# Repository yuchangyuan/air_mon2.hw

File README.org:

#+title: A simple air monitor with multiple sensor

+ data collect with nodemcu-32s
+ WZ-H3/WZ-H3-K for HCOH
+ SGP30 for CO2 & TVOC
+ SHT3X for humidity compensations
+ PMS7003 for PM2.5

current version is v1.1, all sensor works:

+ only test with WZ-H3(manully soldering 2.54mm pin)
+ distance between SHT3X & ESP32 module is too small, cause measured temperature much higher than actual ambient temperature.

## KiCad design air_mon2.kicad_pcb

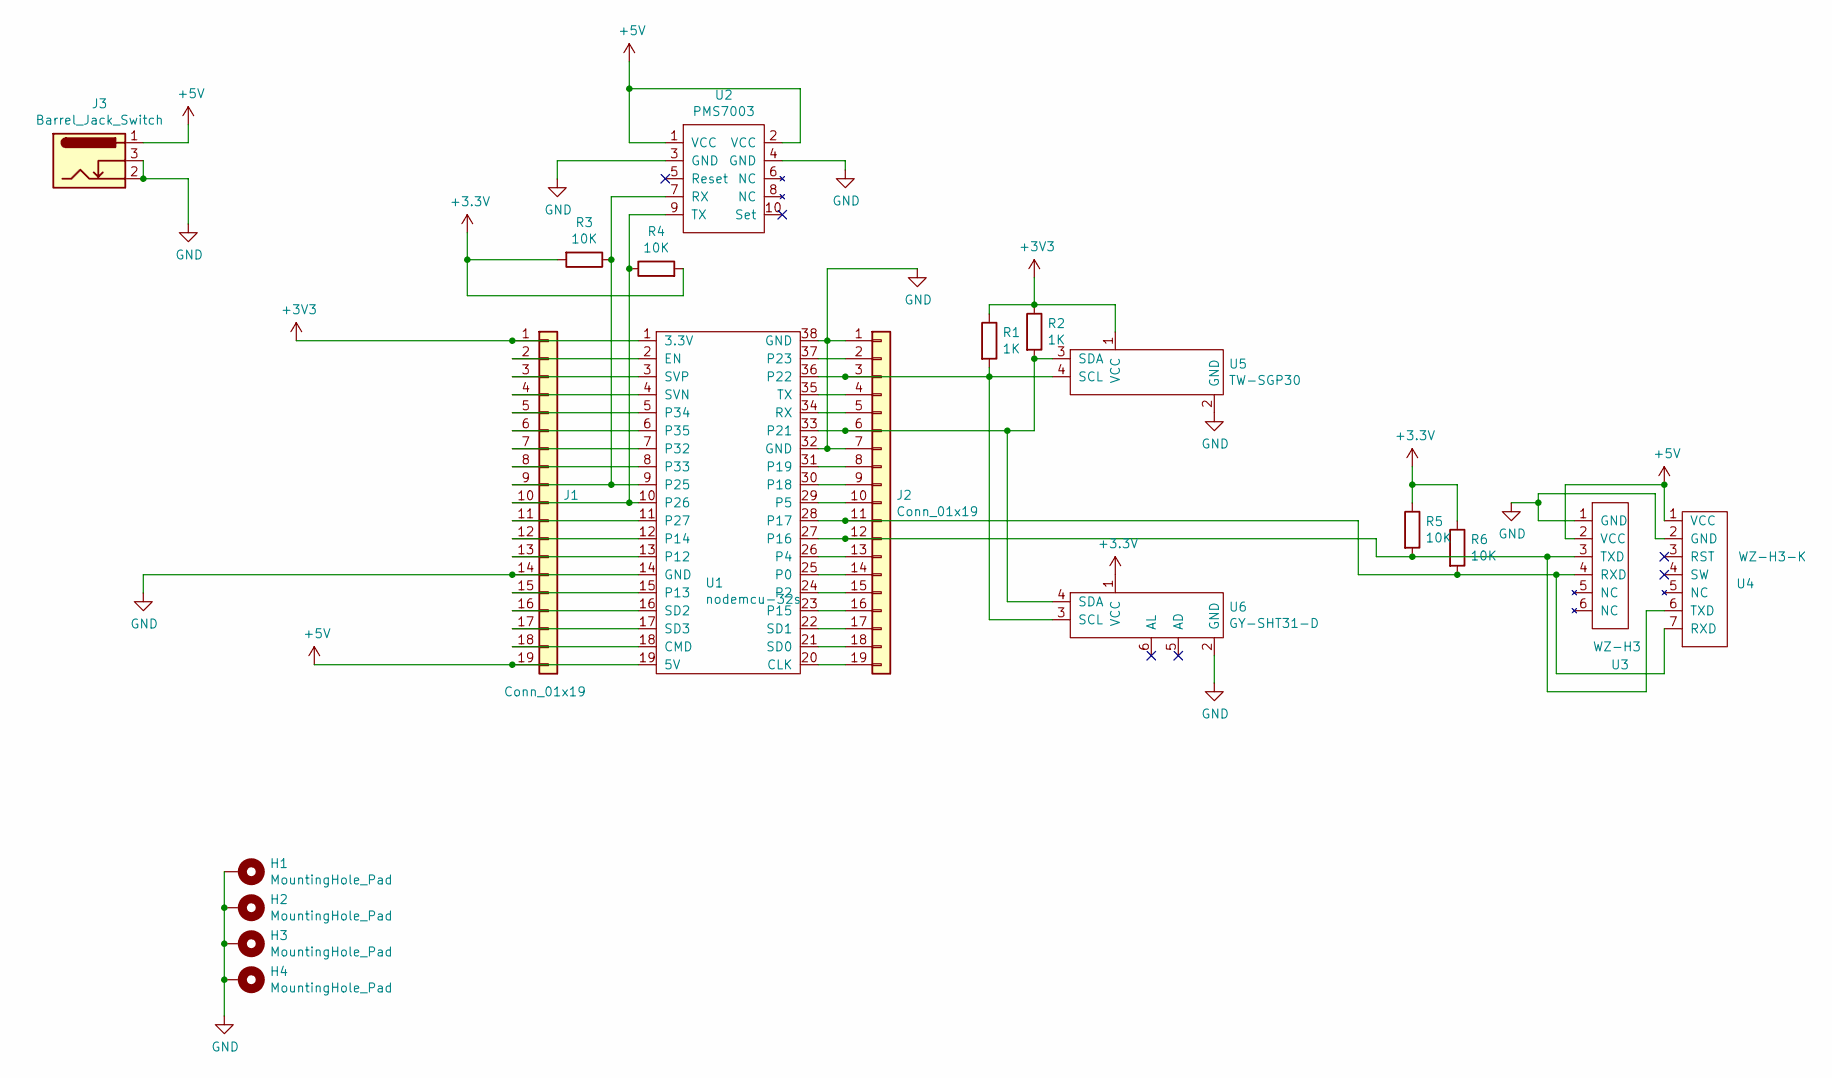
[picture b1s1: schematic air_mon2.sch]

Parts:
H1, H2, H3, H4: MountingHole_Pad; MountingHole_2.2mm_M2_Pad
J1, J2: Conn_01x19; PinHeader_1x19_P2.54mm_Vertical
J3: Barrel_Jack_Switch; BarrelJack_Horizontal
R1, R2: 1K; R_0805_2012Metric_Pad1.20x1.40mm_HandSolder
R3, R4, R5, R6: 10K; R_0805_2012Metric_Pad1.20x1.40mm_HandSolder
U1: nodemcu-32s
U2: PMS7003
U3: WZ-H3
U4: WZ-H3-K
U5: TW-SGP30
U6: GY-SHT31-D

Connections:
+5V: J1.19, J3.1, U1.19 (5V), U2.1 (VCC), U2.2 (VCC), U3.2 (VCC), U4.1 (VCC)
GND: H1.1, H2.1, H3.1, H4.1, J1.14, J2.1, J2.7, J3.2, J3.3, U1.14 (GND), U1.32 (GND), U1.38 (GND), U2.3 (GND), U2.4 (GND), U3.1 (GND), U4.2 (GND), U5.2 (GND), U6.2 (GND)
unnamed: J1.2, U1.2 (EN)
unnamed: J1.3, U1.3 (SVP)
unnamed: J1.4, U1.4 (SVN)
unnamed: J1.5, U1.5 (P34)
unnamed: J1.6, U1.6 (P35)
unnamed: J1.7, U1.7 (P32)
unnamed: J1.8, U1.8 (P33)
unnamed: J1.9, R3.1, U1.9 (P25), U2.7 (RX)
unnamed: J1.10, R4.1, U1.10 (P26), U2.9 (TX)
unnamed: J1.11, U1.11 (P27)
unnamed: J1.12, U1.12 (P14)
unnamed: J1.13, U1.13 (P12)
unnamed: J1.15, U1.15 (P13)
unnamed: J1.16, U1.16 (SD2)
unnamed: J1.17, U1.17 (SD3)
unnamed: J1.18, U1.18 (CMD)
unnamed: J2.2, U1.37 (P23)
unnamed: J2.3, R1.2, U1.36 (P22), U5.4 (SCL), U6.3 (SCL)
unnamed: J2.4, U1.35 (TX)
unnamed: J2.5, U1.34 (RX)
unnamed: J2.6, R2.2, U1.33 (P21), U5.3 (SDA), U6.4 (SDA)
unnamed: J2.8, U1.31 (P19)
unnamed: J2.9, U1.30 (P18)
unnamed: J2.10, U1.29 (P5)
unnamed: J2.11, R6.2, U1.28 (P17), U3.4 (RXD), U4.7 (RXD)
unnamed: J2.12, R5.2, U1.27 (P16), U3.3 (TXD), U4.6 (TXD)
unnamed: J2.13, U1.26 (P4)
unnamed: J2.14, U1.25 (P0)
unnamed: J2.15, U1.24 (P2)
unnamed: J2.16, U1.23 (P15)
unnamed: J2.17, U1.22 (SD1)
unnamed: J2.18, U1.21 (SD0)
unnamed: J2.19, U1.20 (CLK)

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
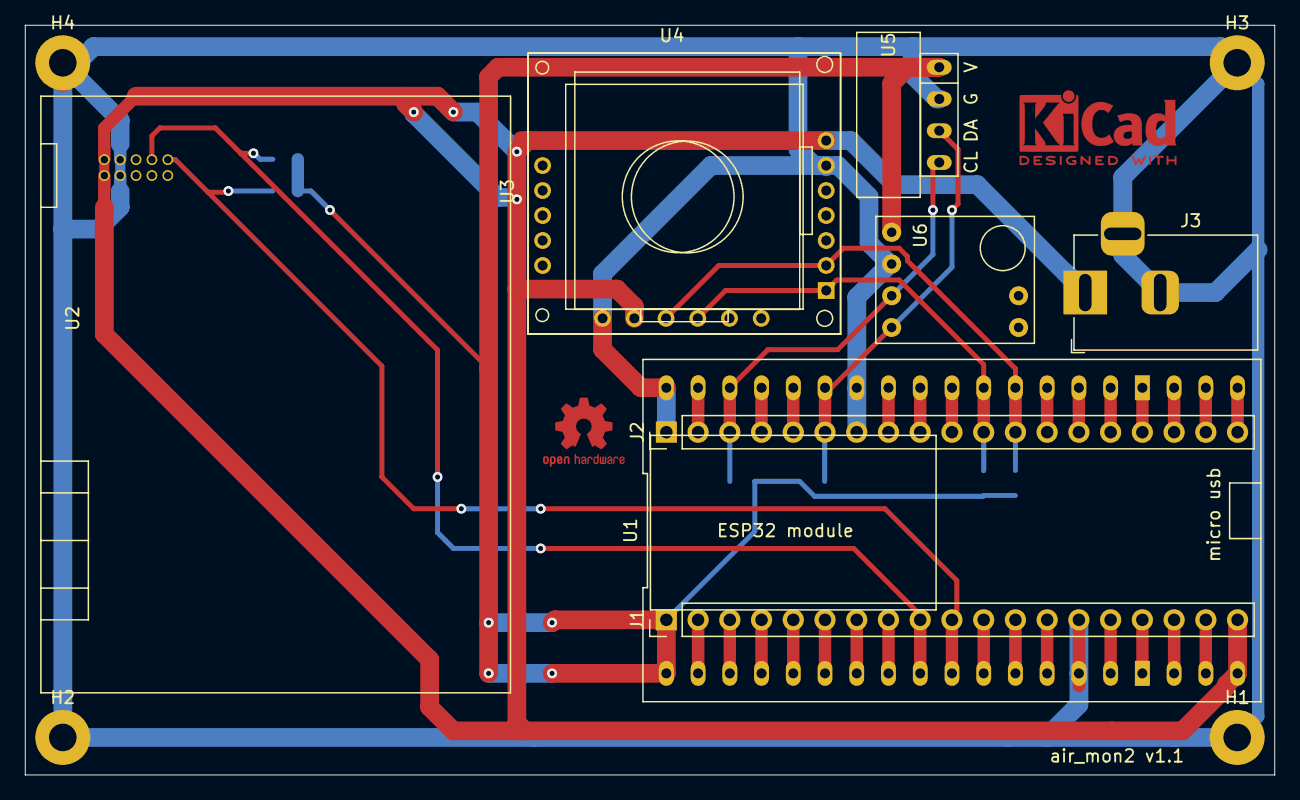
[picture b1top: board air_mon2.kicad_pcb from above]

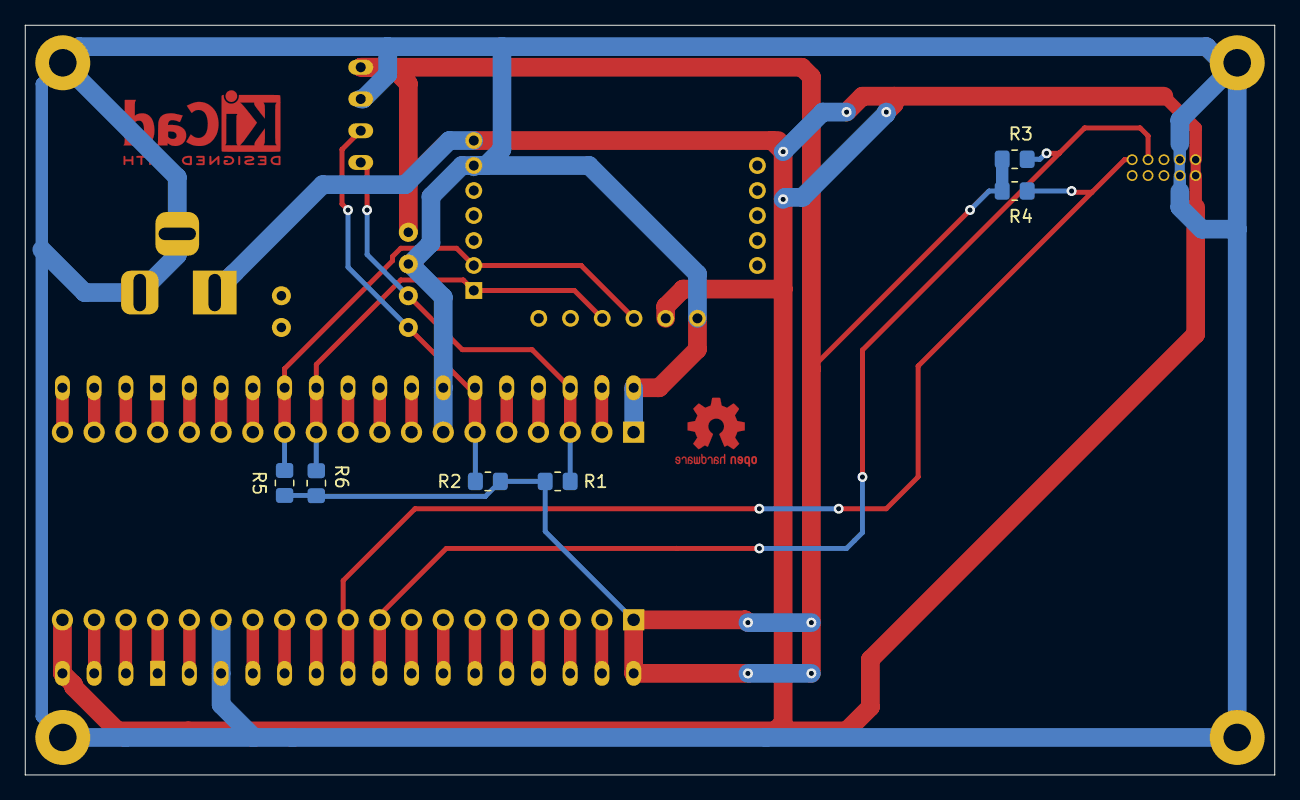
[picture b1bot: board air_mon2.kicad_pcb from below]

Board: 2 copper layers, 100.0 x 60.0 mm, 19 parts (6 on the bottom side), 36 nets.

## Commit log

2021-11-28 v1, has problem
    1. wz-h3 2.54 pin has wrong direction
    2. all txd & rxd need pull up
    3. sgp30 module has no enough distance from dc power jack
    4. need add sth3x sensor
2021-11-28 remove some file
2021-11-28 update, v1.1
    1. add sth31
    2. fix wz-h3
2021-11-28 remove alignment
2021-12-03 Add readme & license
